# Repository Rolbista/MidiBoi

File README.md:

# MidiBoi™

MidiBoi™ is a controller designed for use with Korg® Monologue™. It is literally just two reprogrammable mod wheels.  
Because Monologue™ only has one pitch-stick, dynamic modulation is limited when playing by hand since it's  impossible  
to do, for example, pitch bend and add vibrato at the same time conveniently. LFO int knob is on the other side of  
the synthesizer. Why not use a standard MIDI keyboard with normal wheels then? Well, while standard Pitch Bend MIDI  
message is accepted and interpreted by the synth, Mod Wheel message is not. LFO intensity is assigned to MIDI CC 26  
so it won't react unless you reprogram the wheel to send it. I could not find a controller that would let me do this,  
space was also a consideration - since the Monologue™ already has a keyboard and doesn't exist in a module form apart  
from some risky looking mods, why take up space with another if two wheels are all that is necessary to add  
expressiveness to the interface? Potentiometers with programmable CC messages are useful in cases where hardware is  
fixed and cannot easily accept a different value like you would on a DAW by just using MIDI Learn. While it was built  
with a specific model in mind, this can be used with other synthesizers as well if you need additional mod wheel or  
two or want a comfortable wheel to steer a parameter not present on the panel.

## Setup  

The default selected board is Arduino Pro Micro or clone because of its small size and native USB capability which  
allows you to use it with your DAW without any extra fuss. Every platform and library version is pinned in  
`sketch.yaml`, so a clean checkout compiles identically on any machine. The only prerequisite is  
[arduino-cli](https://arduino.github.io/arduino-cli/) - on macOS, `brew install arduino-cli`. Dependencies download  
automatically on the first build.  

```bash
make build    # compile with the pinned profile
make upload   # compile and flash a connected board
make ports    # list connected boards, if detection fails
make db       # regenerate compile_commands.json + .clangd for the editor
```

Pin assignments live in the constants at the top of `MidiBoi.ino`; adjust them if your wiring differs.

## Usage

MidiBoi™ is powered by USB, just plug one of those old phone chargers that you have lying around that will surely  
come in handy one day - now is their time to shine! Use a standard DIN MIDI cable to connect MidiBoi™ output to  
synth MIDI input. Default CC are 26 (LFO intensity) for wheel 1 and 24 (LFO rate) for wheel 2.  

On power-up the controller reads its configuration from EEPROM - falling back to the defaults if nothing valid is  
stored - and starts in `PLAY` mode, sending the configured messages on channel 1. Clicking the encoder steps through  
the configuration modes and wraps back around:

| Click | Display | Mode |
|-------|---------|------|
| 1 | `P n` | select which wheel to configure |
| 2 | `C nnn` | set that wheel's CC number (0-119) |
| 3 | `L nnn` | set the lowest value that wheel will send |
| 4 | `H nnn` | set the highest value that wheel will send |
| 5 | `PLAY` | back to normal operation |

Turn the encoder to change the displayed value. Edits take effect on returning to `PLAY`.

The lower and upper limits map a wheel's full physical travel onto part of the MIDI range. That helps with instruments  
implementing bipolar modulation by splitting the range in half, where 0-63 is negative and 64-127 positive: setting  
`L` to 63 and `H` to 127 gives positive modulation only, across the whole throw of the wheel, and the bottom of its  
travel reliably returns to neutral. Setting `H` below `L` inverts the response.

CC numbers stop at 119 on purpose. 120-127 are Channel Mode messages - All Sound Off, Reset All Controllers, All Notes  
Off - and sweeping a wheel through those would badly misbehave on the receiving instrument.

To save potentiometer settings to persistent memory double press the encoder while in `PLAY` mode.  
A `SAVE` message displays for one second and returns to normal.  

## Features

* Segment display showing current wheel/potentiometer/MIDI CC selected
* Encoder for value input
* Support for n potentiometers with reprogrammable CCs limited only by number of ADC pins on selected Arduino board
* Support for storing and saving potentiometer configs in EEPROM  
* Per-wheel output range, for instruments that split the MIDI range into bipolar modulation halves  
* USB and DIN5 MIDI output on channel 1
* Extensibility: with little modification of the hardware any MIDI parameter can be controlled with any type of analog device - add a jack for an expression pedal if you like

## Roadmap  

* Software MIDI passthrough so the only DIN jack on target synth is not taken up
* Possibly OLED screen for clearer information display
* Channel reprogrammability
* Higher bit resolution (10 bit, allowed by Control-Surface library)
* Example PCB design (Kicad single-sided board)

## Additional info

Libraries used:  
https://github.com/tttapa/Control-Surface  
https://github.com/mathertel/RotaryEncoder  
https://github.com/avishorp/TM1637  
https://github.com/mathertel/OneButton  

Monologue MIDI Implementation Chart:  
https://www.korg.com/us/support/download/manual/0/733/3519/  
https://bit.ly/2ZH0zTO (page 58)

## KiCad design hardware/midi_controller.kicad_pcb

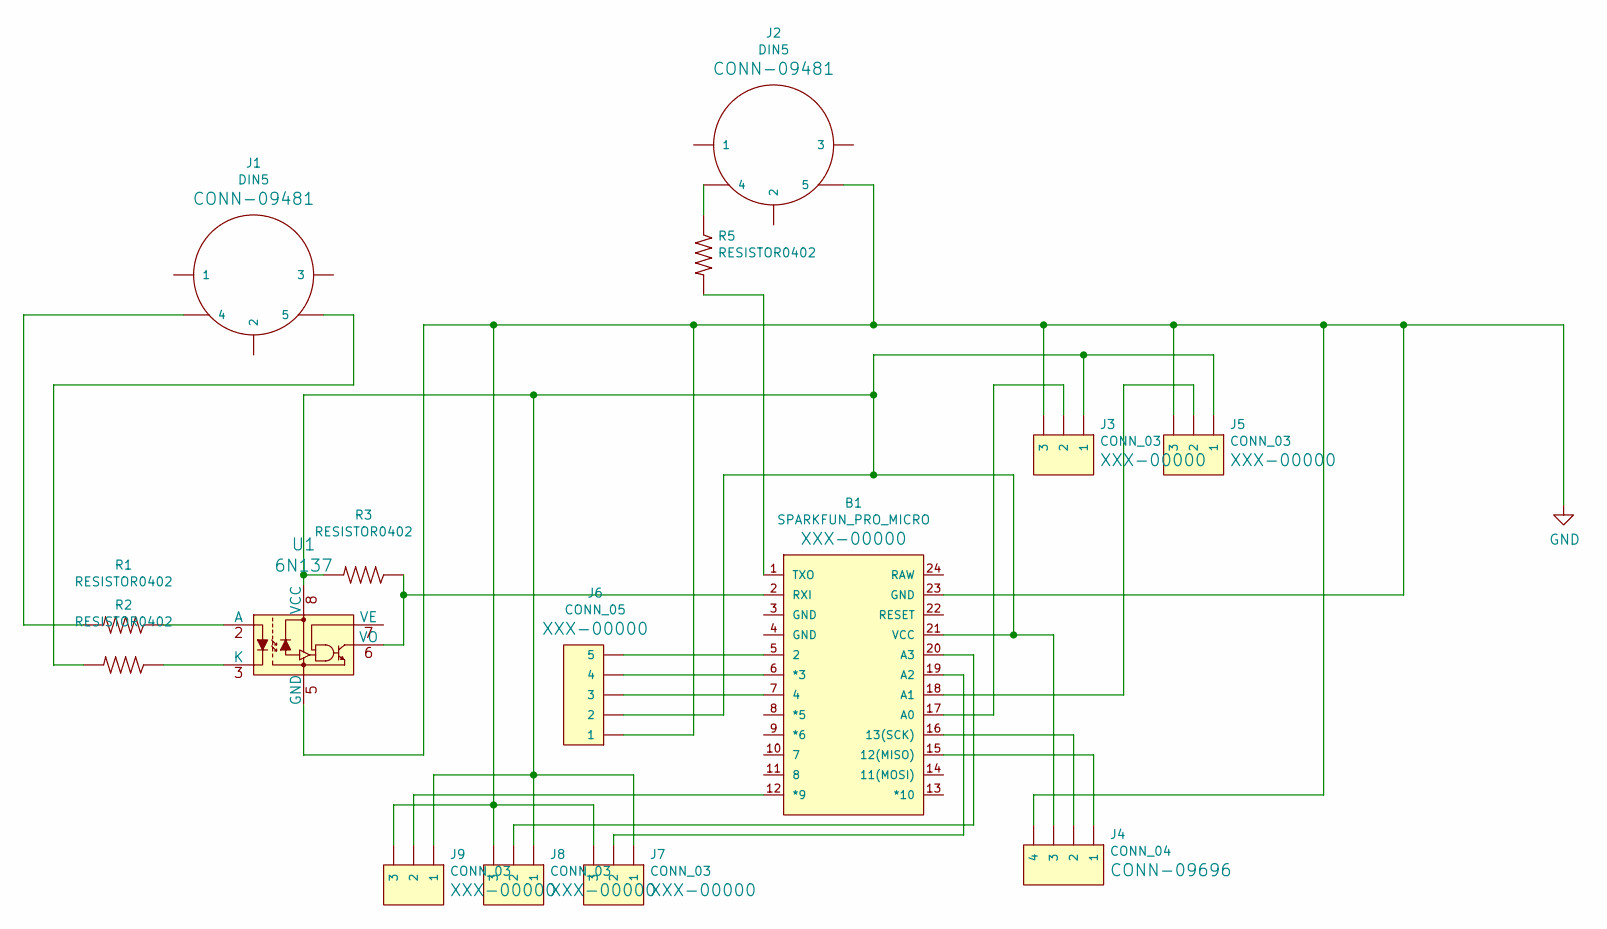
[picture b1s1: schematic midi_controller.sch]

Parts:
B1: SPARKFUN_PRO_MICRO
J1, J2: DIN5; DIN5-RA-PTH
J3, J5, J7, J8, J9: CONN_03; 1X03
J4: CONN_04; 1X04
J6: CONN_05; 1X05
R1, R2, R3, R5: RESISTOR0402; Resistor_SMD+THTuniversal_2512_RM10_HandSoldering_RevA_Date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
U1: 6N137; DIP-8_W7.62mm; MPN 6N137; Digi-Key_PN 160-1791-ND

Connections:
GND: B1.23 (GND), J2.5, J3.3, J4.4, J5.3, J6.1, J7.3, J8.3, J9.3, U1.5 (GND)
unnamed: B1.1 (TXO), R5.2
unnamed: B1.2 (RXI), R3.1, U1.6 (VO)
unnamed: B1.5 (2), J6.5
unnamed: B1.6 (*3), J6.4
unnamed: B1.7 (4), J6.3
unnamed: B1.12 (*9), J9.2
unnamed: B1.15 (12(MISO)), J4.1
unnamed: B1.16 (13(SCK)), J4.2
unnamed: B1.17 (A0), J3.2
unnamed: B1.18 (A1), J5.2
unnamed: B1.19 (A2), J7.2
unnamed: B1.20 (A3), J8.2
unnamed: B1.21 (VCC), J3.1, J4.3, J5.1, J6.2, J7.1, J8.1, J9.1, R3.2, U1.8 (VCC)
unnamed: J1.4, R1.2
unnamed: J1.5, R2.2
unnamed: J2.4, R5.1
unnamed: R1.1, U1.2 (A)
unnamed: R2.1, U1.3 (K)

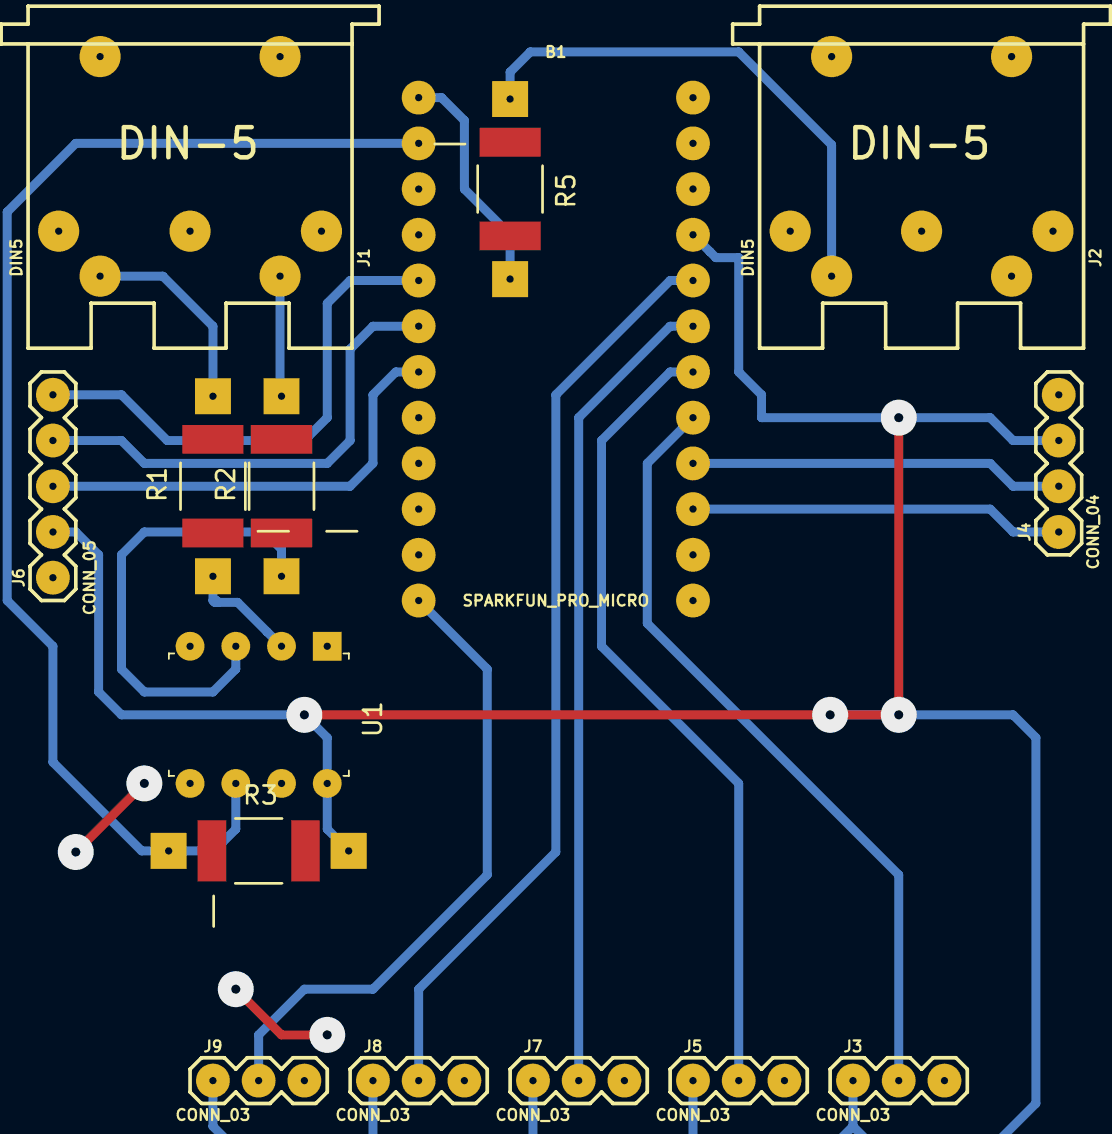
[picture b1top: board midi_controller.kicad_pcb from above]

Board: 2 copper layers, 15 parts (0 on the bottom side), 19 nets.

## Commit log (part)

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2021-09-07 test message
2024-06-16 update Control Sufrace library version, enable DIN midi, update naming to remove compiler warnings
2024-06-18 squash this
